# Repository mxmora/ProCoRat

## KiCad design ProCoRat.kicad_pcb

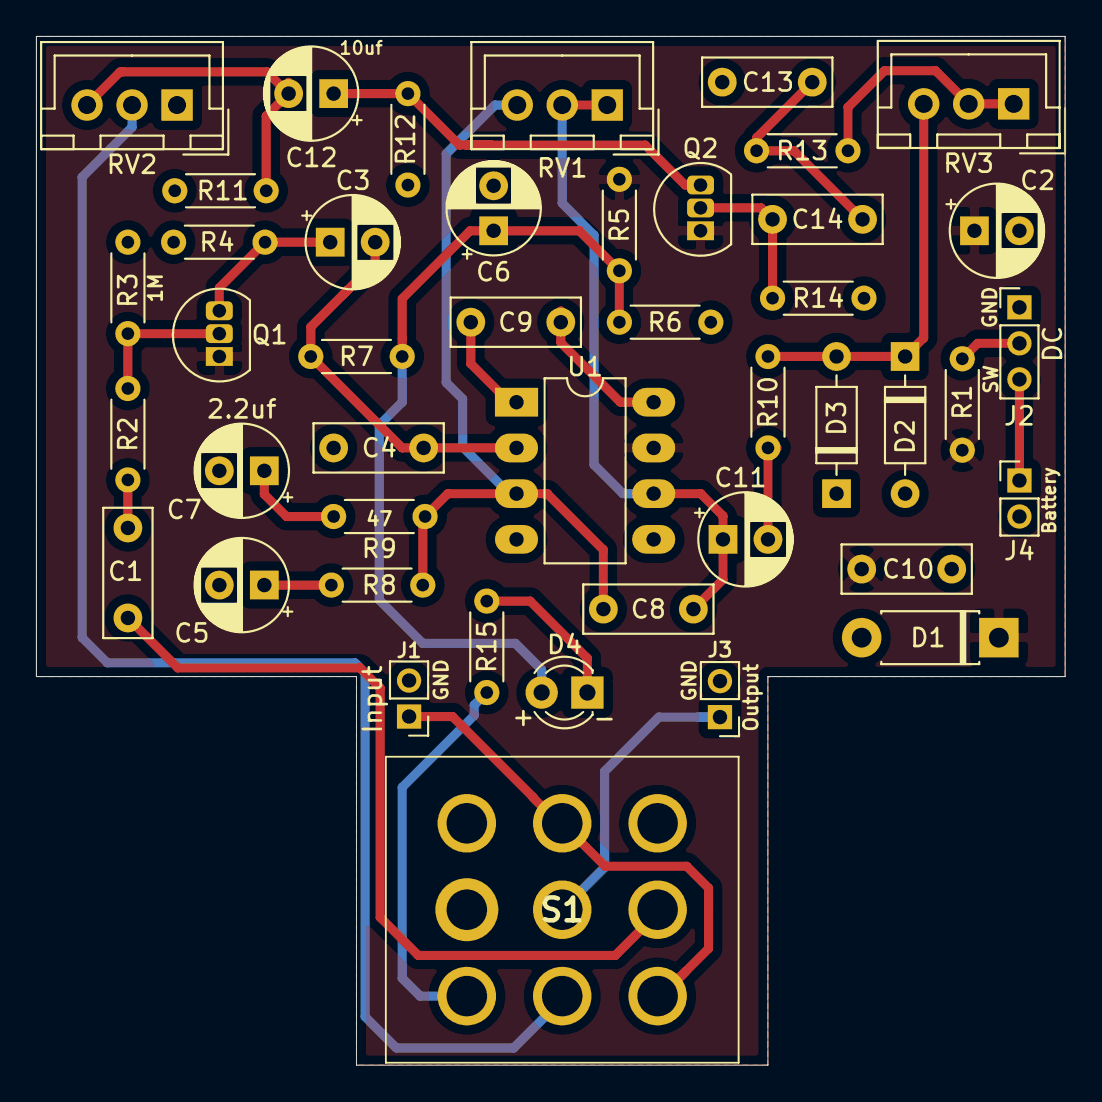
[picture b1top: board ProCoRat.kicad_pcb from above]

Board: 2 copper layers, 57.2 x 57.1 mm, 44 parts (0 on the bottom side), 28 nets.

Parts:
C1, C14: .022uf; C_Rect_L7.0mm_W2.5mm_P5.00mm
C2: 100uf; CP_Radial_D5.0mm_P2.50mm
C3: 1uf; CP_Radial_D5.0mm_P2.50mm
C4: 1nf; C_Rect_L7.0mm_W2.5mm_P5.00mm
C5, C11: 4.7uf; CP_Radial_D5.0mm_P2.50mm
C6: 47uf; CP_Radial_D5.0mm_P2.50mm
C7: 2.2uf; CP_Radial_D5.0mm_P2.50mm
C8: 100pf; C_Rect_L7.0mm_W2.5mm_P5.00mm
C9: 30pf; C_Rect_L7.0mm_W2.5mm_P5.00mm
C10: .001uf; C_Rect_L7.0mm_W2.5mm_P5.00mm
C12: 10uf; CP_Radial_D5.0mm_P2.50mm
C13: .0033uf; C_Rect_L7.0mm_W2.5mm_P5.00mm
D1: 1N4001; D_DO-41_SOD81_P7.62mm_Horizontal
D2, D3: 1N4148; D_DO-35_SOD27_P7.62mm_Horizontal
D4: LED; LED_D3.0mm
J1: Input; PinHeader_1x02_P2.00mm_Vertical
J2: DC; PinHeader_1x03_P2.00mm_Vertical
J3: Output; PinHeader_1x02_P2.00mm_Vertical
J4: Battery; PinHeader_1x02_P2.00mm_Vertical
Q1, Q2: J113; TO-92L_Inline
R1, R9: 47; R_Axial_DIN0204_L3.6mm_D1.6mm_P5.08mm_Horizontal
R2, R4, R10, R12, R15: 1k; R_Axial_DIN0204_L3.6mm_D1.6mm_P5.08mm_Horizontal
R3, R14: 1M; R_Axial_DIN0204_L3.6mm_D1.6mm_P5.08mm_Horizontal
R5, R6: 33k; R_Axial_DIN0204_L3.6mm_D1.6mm_P5.08mm_Horizontal
R7: 100k; R_Axial_DIN0204_L3.6mm_D1.6mm_P5.08mm_Horizontal
R8: 560; R_Axial_DIN0204_L3.6mm_D1.6mm_P5.08mm_Horizontal
R11: 10k; R_Axial_DIN0204_L3.6mm_D1.6mm_P5.08mm_Horizontal
R13: 1.5k; R_Axial_DIN0204_L3.6mm_D1.6mm_P5.08mm_Horizontal
RV1: 150k log; JST_XH_B03B-XH-A_03x2.50mm_Straight
RV2, RV3: 100k Log; JST_XH_B03B-XH-A_03x2.50mm_Straight
S1: SF17020F-0302-21R-L-015; SF17020F030221RL015
U1: LM308; DIP-8_W7.62mm_LongPads

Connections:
4.5v: C6.1, D4.2, R5.1, R6.2, R7.2
9V: C2.1, C10.1, D1.1, Q1.1, Q2.1, R1.1, R5.2, U1.7
GND: C2.2, C4.1, C5.2, C6.2, C7.2, C10.2, C13.1, D1.2, D2.2, D3.1, J1.2, J2.1, J3.2, J4.2, R3.1, R4.1, R6.1, R11.1, R12.1, R14.1, RV2.1, S1.3, S1.8, U1.4
unnamed: C1.1, R2.2
unnamed: C1.2, S1.2
unnamed: C3.1, Q1.3, R4.2
unnamed: C3.2, C4.2, R7.1, U1.2
unnamed: C5.1, R8.1
unnamed: C7.1, R9.1
unnamed: C8.1, R8.2, R9.2, RV1.3, U1.3
unnamed: C9.1, U1.1
unnamed: C9.2, U1.8
unnamed: C8.2, C11.1, RV1.1, RV1.2, U1.6
unnamed: C11.2, R10.1
unnamed: C12.1, Q2.3, R12.2
unnamed: C12.2, R11.2, RV2.3
unnamed: C13.2, C14.2, R13.2
unnamed: C14.1, Q2.2, R14.2
unnamed: D2.1, D3.2, R10.2, RV3.3
unnamed: D4.1, R15.1
unnamed: J1.1, S1.1, S1.6
unnamed: J2.2, R1.2
unnamed: J2.3, J4.1
unnamed: J3.1, S1.5
unnamed: Q1.2, R2.1, R3.2
unnamed: R13.1, RV3.1, RV3.2
unnamed: R15.2, S1.7
Output: RV2.2, S1.4

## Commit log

2019-07-09 Refine the board. Fix a few errors.
